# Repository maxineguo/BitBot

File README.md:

# BitBot

The BitBot is a PCB with the XIAO RP2040, an accelerometer, 2 buttons, and a screen. The screen displays a small person who does random actions from time to time. You can interact with this person by either tilting the PCB or by pressing the Add Person and Reset buttons.

## Screenshots!
Schematic

PCB

Front

Back

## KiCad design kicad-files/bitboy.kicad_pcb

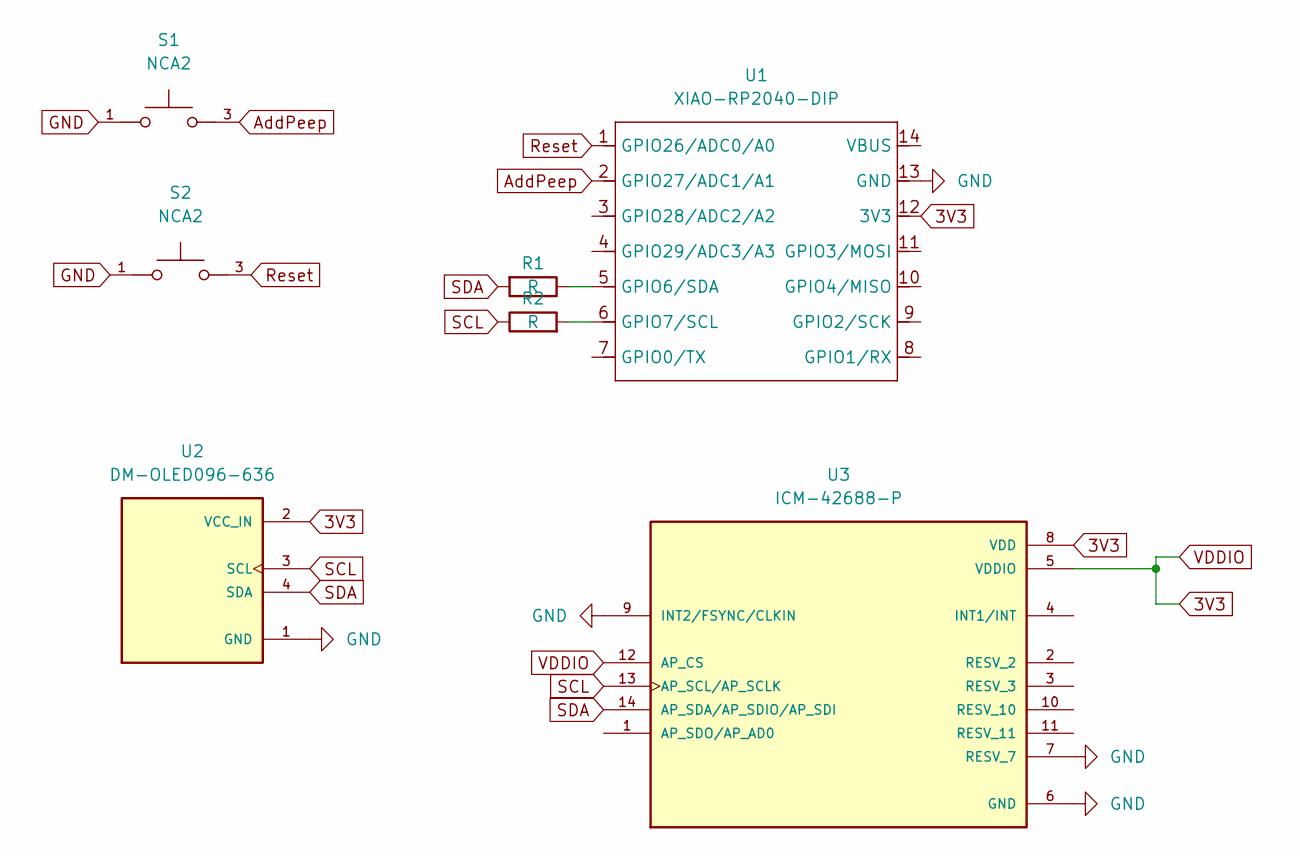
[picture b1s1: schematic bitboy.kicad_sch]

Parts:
R1, R2: R; XTAL_ZTA-2.44MG
S1, S2: NCA2; SW_NCA2; PARTREV B
U1: XIAO-RP2040-DIP; MCU_Seeed_ESP32C3
U2: DM-OLED096-636; MODULE_DM-OLED096-636; PARTREV 2018-09-10
U3: ICM-42688-P; PQFN50P300X250X97-14N; PARTREV 1.2

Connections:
3V3: U1.12 (3V3), U2.2 (VCC_IN), U3.5 (VDDIO), U3.8 (VDD), U3.12 (AP_CS)
AddPeep: S1.3, U1.2 (GPIO27/ADC1/A1)
GND: S1.1, S2.1, U1.13 (GND), U2.1 (GND), U3.6 (GND), U3.7 (RESV_7), U3.9 (INT2/FSYNC/CLKIN)
unnamed: R2.1, U1.5 (GPIO6/SDA)
unnamed: R1.2, U1.6 (GPIO7/SCL)
Reset: S2.3, U1.1 (GPIO26/ADC0/A0)
SCL: R1.1, U2.3 (SCL), U3.13 (AP_SCL/AP_SCLK)
SDA: R2.2, U2.4 (SDA), U3.14 (AP_SDA/AP_SDIO/AP_SDI)

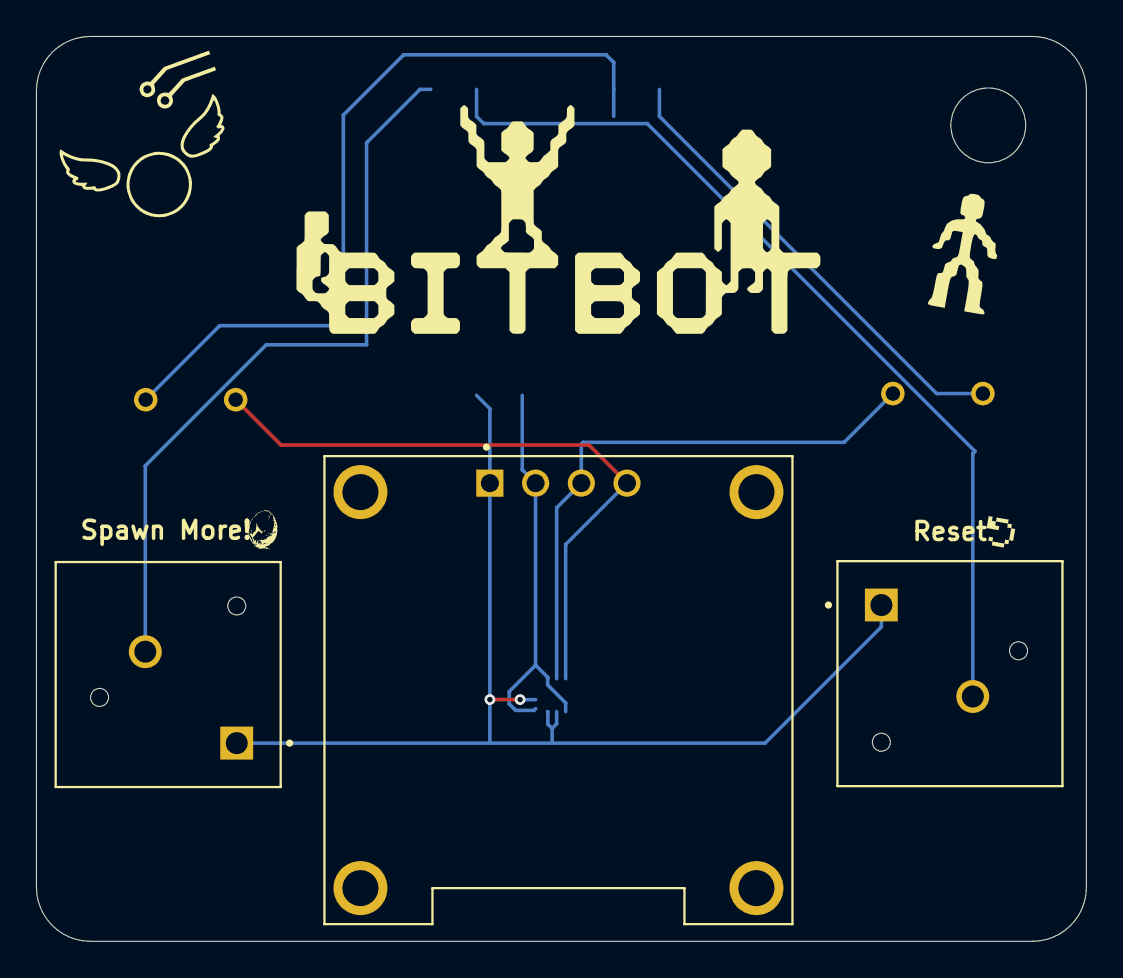
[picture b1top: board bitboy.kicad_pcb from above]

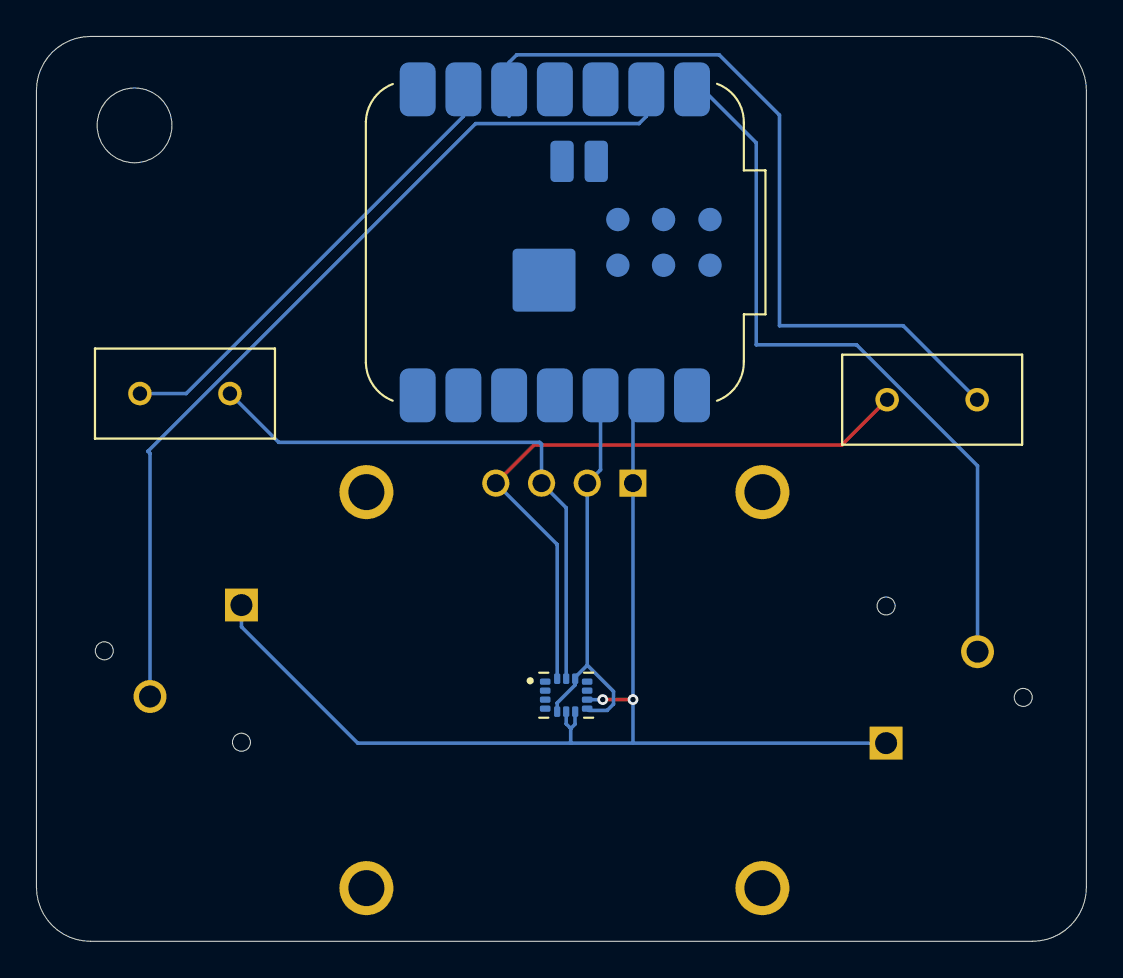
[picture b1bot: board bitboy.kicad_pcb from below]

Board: 2 copper layers, 58.3 x 50.3 mm, 7 parts (4 on the bottom side), 8 nets.

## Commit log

2025-07-28 Add kicad files
2025-08-01 Set up firmware(no functionallity)
2025-08-01 reorganize
2025-08-01 Finish code
2025-08-01 Add screenshots
2025-08-01 Add prod folder
2025-08-02 final edits
